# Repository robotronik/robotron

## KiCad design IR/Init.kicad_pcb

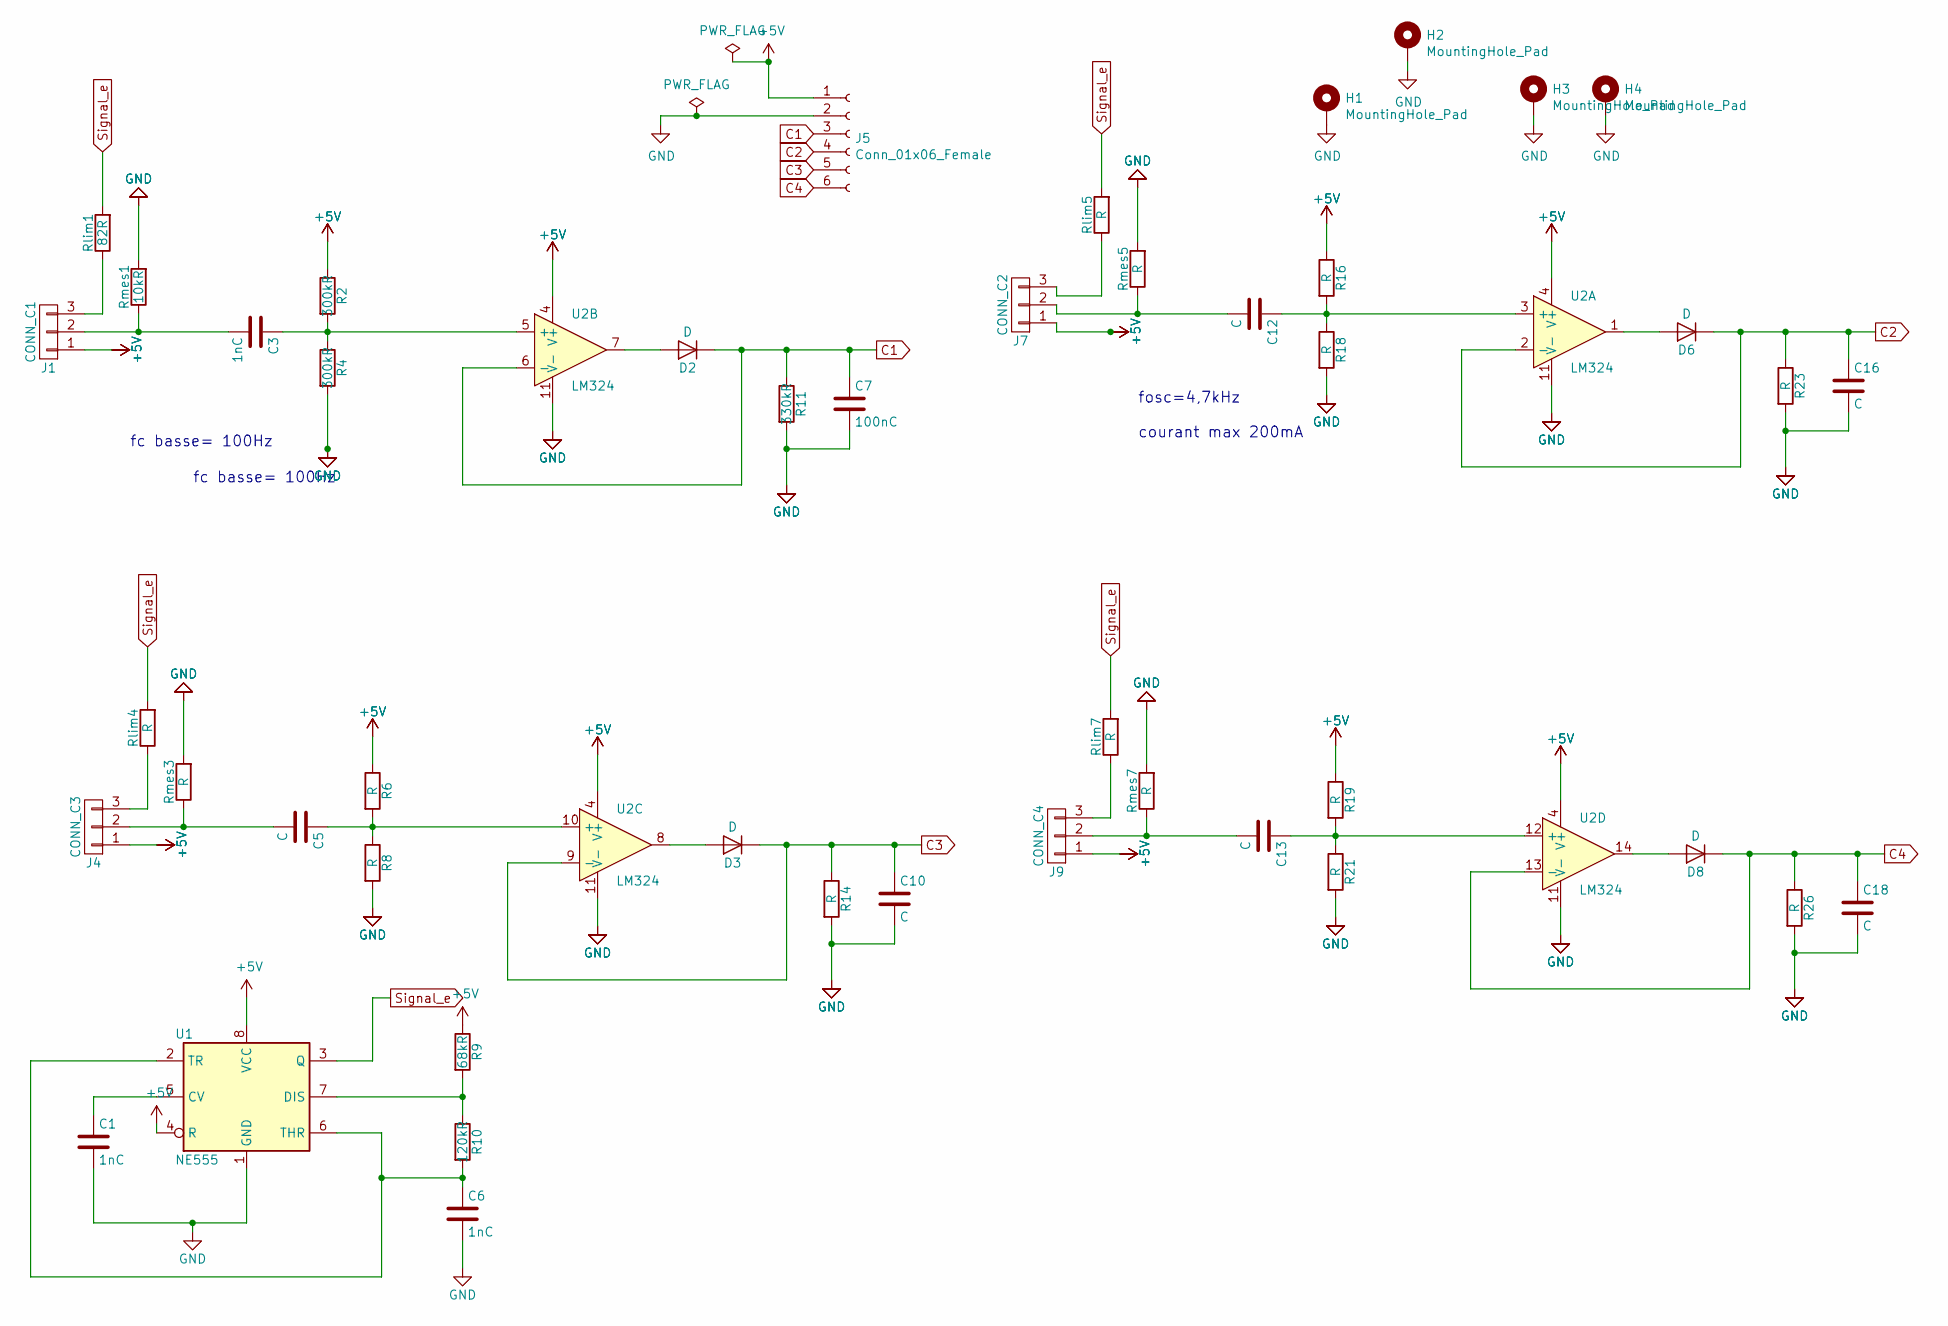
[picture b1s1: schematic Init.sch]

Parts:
C1, C3, C6: 1nC; C_Rect_L7.0mm_W2.5mm_P5.00mm
C5, C10, C12, C13, C16, C18: C; C_Rect_L7.0mm_W2.5mm_P5.00mm
C7: 100nC; C_Rect_L7.0mm_W2.5mm_P5.00mm
D2, D3, D6, D8: D; D_A-405_P10.16mm_Horizontal
H1, H2, H3, H4: MountingHole_Pad; MountingHole_3.2mm_M3_DIN965_Pad
J1: CONN_C1; Molex_KK-254_AE-6410-03A_1x03_P2.54mm_Vertical
J4: CONN_C3; Molex_KK-254_AE-6410-03A_1x03_P2.54mm_Vertical
J5: Conn_01x06_Female; PinHeader_1x06_P2.54mm_Vertical
J7: CONN_C2; Molex_KK-254_AE-6410-03A_1x03_P2.54mm_Vertical
J9: CONN_C4; Molex_KK-254_AE-6410-03A_1x03_P2.54mm_Vertical
R2, R4: 300kR; R_Axial_DIN0207_L6.3mm_D2.5mm_P10.16mm_Horizontal
R6, R8, R14, R16, R18, R19, R21, R23, R26: R; R_Axial_DIN0207_L6.3mm_D2.5mm_P10.16mm_Horizontal
R9: 68kR; R_Axial_DIN0207_L6.3mm_D2.5mm_P10.16mm_Horizontal
R10: 120kR; R_Axial_DIN0207_L6.3mm_D2.5mm_P10.16mm_Horizontal
R11: 330kR; R_Axial_DIN0207_L6.3mm_D2.5mm_P10.16mm_Horizontal
Rlim1: 82R; R_Axial_DIN0207_L6.3mm_D2.5mm_P10.16mm_Horizontal
Rlim4, Rlim5, Rlim7: R; R_Axial_DIN0207_L6.3mm_D2.5mm_P10.16mm_Horizontal
Rmes1: 10kR; R_Axial_DIN0207_L6.3mm_D2.5mm_P10.16mm_Horizontal
Rmes3, Rmes5, Rmes7: R; R_Axial_DIN0207_L6.3mm_D2.5mm_P10.16mm_Horizontal
U1: NE555; DIP-8_W7.62mm
U2: LM324; DIP-14_W7.62mm

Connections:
+5V: J1.1, J4.1, J5.1, J7.1, J9.1, R2.1, R6.1, R9.1, R16.1, R19.1, U1.4 (R), U1.8 (VCC), U2.4 (V+)
C1: C7.1, D2.1 (K), J5.3, R11.1, U2.6 (-)
C2: C16.1, D6.1 (K), J5.4, R23.1, U2.2 (-)
C3: C10.1, D3.1 (K), J5.5, R14.1, U2.9 (-)
C4: C18.1, D8.1 (K), J5.6, R26.1, U2.13 (-)
GND: C1.2, C6.2, C7.2, C10.2, C16.2, C18.2, H1.1, H2.1, H3.1, H4.1, J5.2, R4.2, R8.2, R11.2, R14.2, R18.2, R21.2, R23.2, R26.2, Rmes1.2, Rmes3.2, Rmes5.2, Rmes7.2, U1.1 (GND), U2.11 (V-)
unnamed: C1.1, U1.5 (CV)
unnamed: C3.1, R2.2, R4.1, U2.5 (+)
unnamed: C3.2, J1.2, Rmes1.1
unnamed: C5.1, R6.2, R8.1, U2.10 (+)
unnamed: C5.2, J4.2, Rmes3.1
unnamed: C6.1, R10.2, U1.2 (TR), U1.6 (THR)
unnamed: C12.1, R16.2, R18.1, U2.3 (+)
unnamed: C12.2, J7.2, Rmes5.1
unnamed: C13.1, R19.2, R21.1, U2.12 (+)
unnamed: C13.2, J9.2, Rmes7.1
unnamed: D2.2 (A), U2.7
unnamed: D3.2 (A), U2.8
unnamed: D6.2 (A), U2.1
unnamed: D8.2 (A), U2.14
unnamed: J1.3, Rlim1.1
unnamed: J4.3, Rlim4.1
unnamed: J7.3, Rlim5.1
unnamed: J9.3, Rlim7.1
unnamed: R9.2, R10.1, U1.7 (DIS)
Signal_e: Rlim1.2, Rlim4.2, Rlim5.2, Rlim7.2, U1.3 (Q)

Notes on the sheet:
fc basse= 100Hz
fosc=4,7kHz courant max 200mA

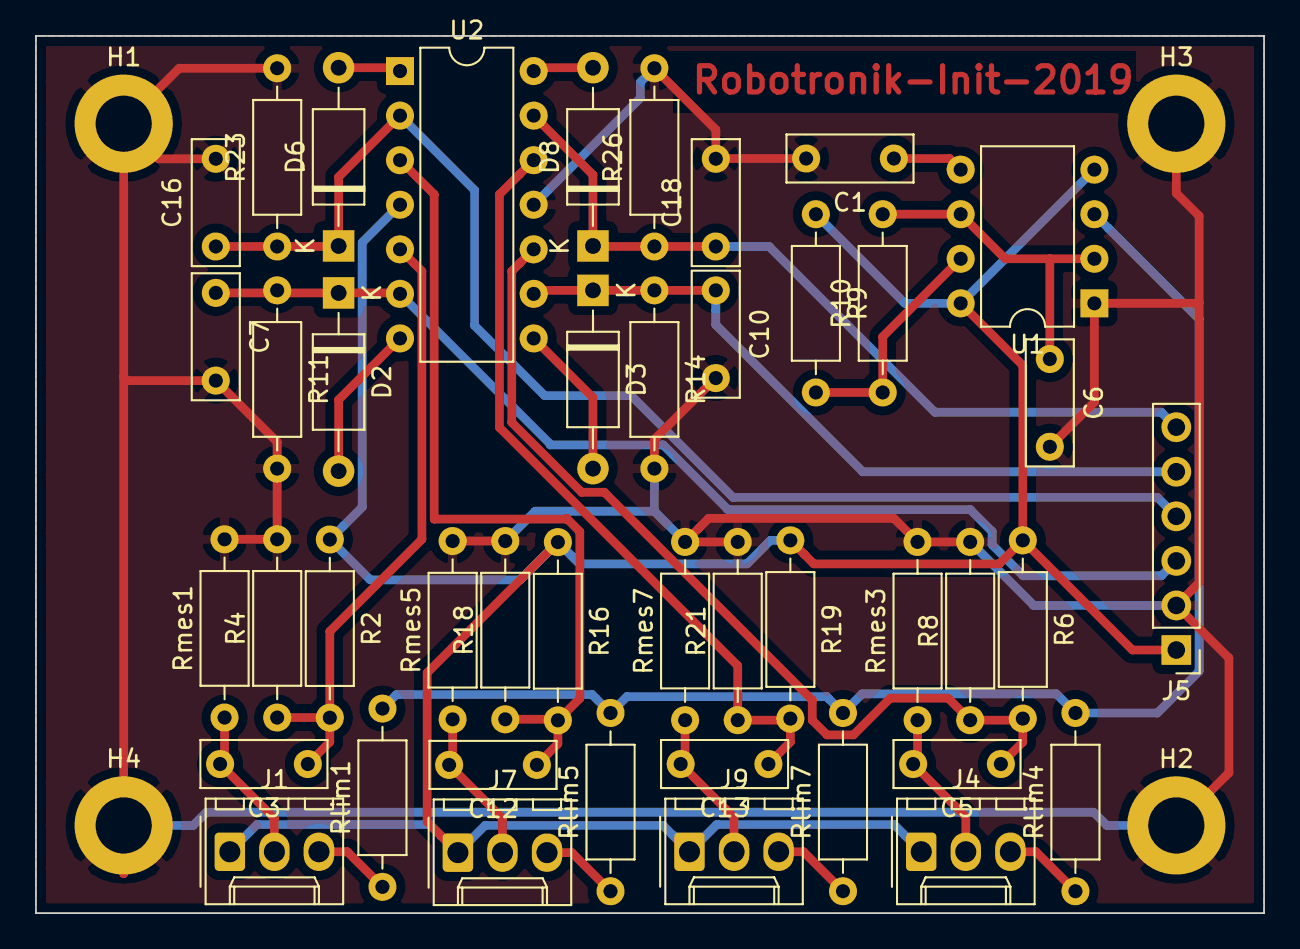
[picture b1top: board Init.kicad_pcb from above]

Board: 2 copper layers, 70.0 x 50.0 mm, 47 parts (0 on the bottom side), 26 nets.

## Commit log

2019-09-10 ajout kicad IR
2019-09-12 PCB prototype
